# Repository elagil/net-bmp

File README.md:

# net bmp

An Ethernet-connected SWD/JTAG debug adapter, based on the [blackmagic probe](https://black-magic.org).

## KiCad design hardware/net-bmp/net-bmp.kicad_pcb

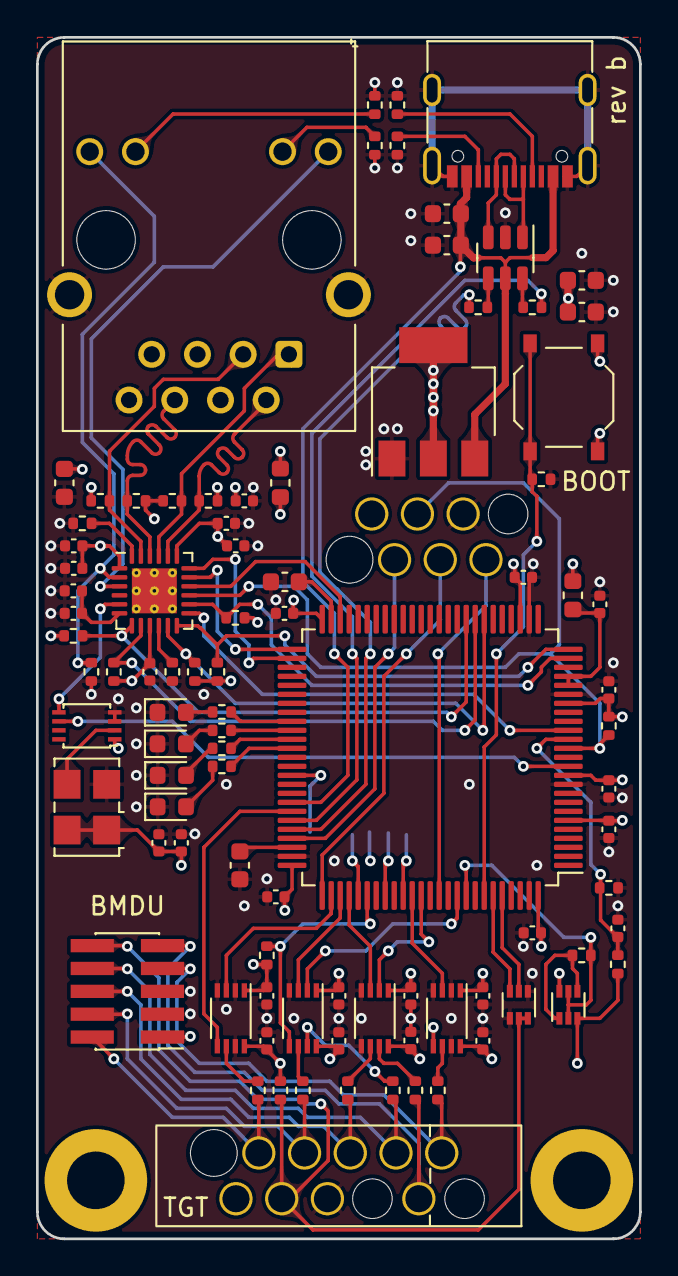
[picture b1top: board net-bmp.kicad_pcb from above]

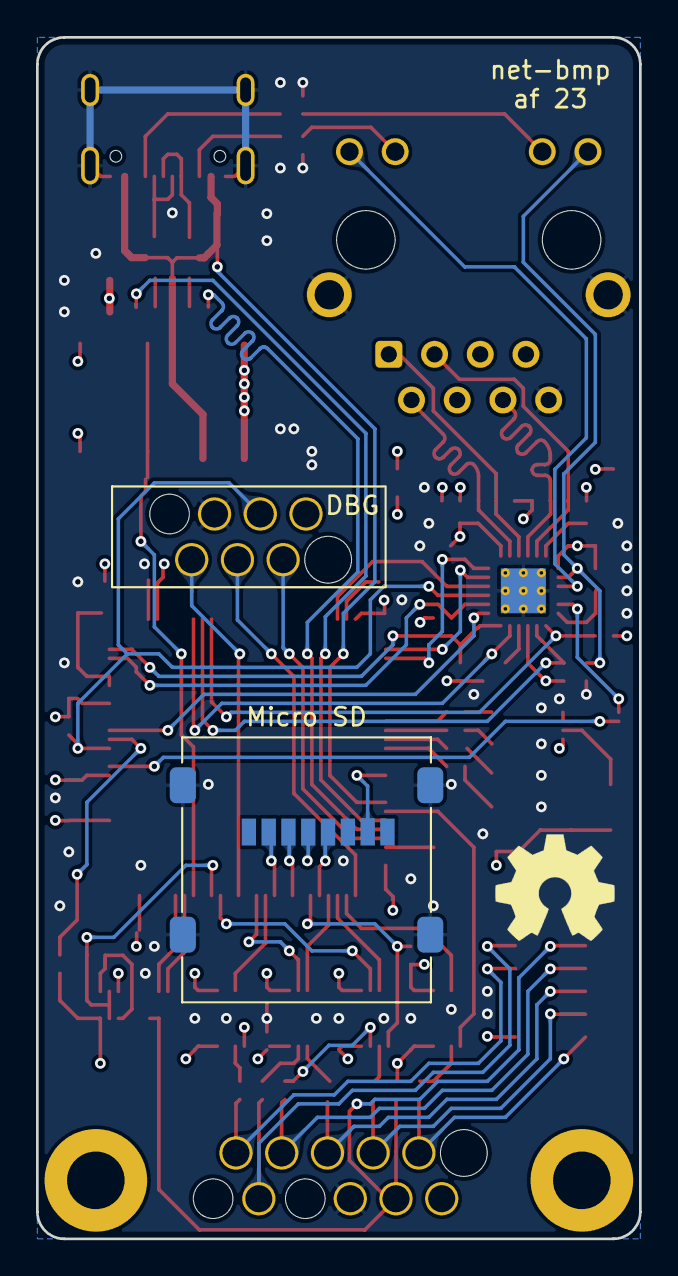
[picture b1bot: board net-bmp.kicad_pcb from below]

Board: 4 copper layers, 33.5 x 66.8 mm, 97 parts (3 on the bottom side), 82 nets.

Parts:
C1, C2, C3, C4, C5, C6, C7, C8, C11, C12, C13, C14, C15, C16, C17, C18, C21, C22, C23, C24, C25, C33, C35: 100n; C_0402_1005Metric
C9, C10: 2.2u; C_0603_1608Metric
C19: 1n; C_0402_1005Metric
C20: 1u; C_0402_1005Metric
C26, C28, C29, C30, C31: 10u; C_0603_1608Metric
C27: 22n; C_0402_1005Metric
C34: 10n; C_0402_1005Metric
D1: Blue; LED_0603_1608Metric
D2: Green; LED_0603_1608Metric
D3: Yellow; LED_0603_1608Metric
D4: Red; LED_0603_1608Metric
FB1, FB2: FerriteBead; L_0603_1608Metric
H1, H2: MountingHole; MountingHole_3.2mm_M3_ISO7380_Pad
J1: DBG; WR-WST REDFIT IDC 6 DBG
J2: Micro SD; microSD_HC_Molex_47219-2001
J4: USB_C_Receptacle_USB2.0; USB_C_Receptacle_G-Switch_GT-USB-7010ASV
J5: TGT; WR-WST REDFIT IDC 6 10 DBG
J6: BMDU; PinHeader_2x05_P1.27mm_Vertical_SMD
J7: HR911105A; RJ45_Hanrun_HR911105A
Q1, Q2: DMG1024UV-7; SOT-563
R1, R2, R7, R14, R15, R16, R17, R18, R19, R21, R35, R37: 10k; R_0402_1005Metric
R3, R4, R5, R6, R27, R28: 330; R_0402_1005Metric
R8, R9, R10, R11, R12, R13, R29, R30: 33; R_0402_1005Metric
R20: 1.5k; R_0402_1005Metric
R22: 12k; R_0402_1005Metric
R23, R24, R25, R26: 49.9; R_0402_1005Metric
R33, R34, R36: 5.1k; R_0402_1005Metric
SW1: SW_SPST; SW_Push_1P1T_XKB_TS-1187A
U1: STM32F407VETx; LQFP-100_14x14mm_P0.5mm
U2, U3, U4, U5: 74LVC2T45DC; VSSOP-8_2.3x2mm_P0.5mm
U6: LAN8742A; VQFN-24-1EP_4x4mm_P0.5mm_EP2.5x2.5mm_ThermalVias
U7: USBLC6-2SC6; SOT-23-6
U8: AMS1117-3.3; SOT-223-3_TabPin2
U9: 74AVC9112; VSSOP-8_2.4x2.1mm_P0.5mm
X2: SG-5032CCN; Oscillator_SMD_SeikoEpson_SG8002LB-4Pin_5.0x3.2mm
oshw1: Logo_Open_Hardware_Large; OSHW-Symbol_6.7x6mm_SilkScreen

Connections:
+3.3V: C1.1, C2.1, C3.1, C4.1, C5.1, C6.1, C7.1, C11.1, C12.1, C13.1, C14.1, C21.1, C30.1, C31.1, C33.1, C34.1, FB1.2, FB2.1, J1.1 (VREF), J2.4 (VDD), Q2.6 (D), R1.2, R7.2, R16.2, R17.2, R18.2, R19.2, R20.2, SW1.2 (B), U1.6 (VBAT), U1.11 (VDD), U1.19 (VDD), U1.28 (VDD), U1.50 (VDD), U1.75 (VDD), U1.100 (VDD), U2.1 (VCCA), U2.5 (DIR), U3.1 (VCCA), U4.1 (VCCA), U5.1 (VCCA), U6.9 (VDDIO), U8.2 (VO), U9.1 (VCC), X2.1 (OE), X2.4 (Vcc)
+3.3VA: C22.1, C23.1, C24.1, C25.1, C26.1, C27.2, FB1.1, J7.4, J7.5, R23.2, R24.2, R25.2, R26.2, U6.1 (VDD2A), U6.19 (VDD1A)
+3.3VP: C8.1, FB2.2, U1.21 (VREF+), U1.22 (VDDA)
/BOOT: R2.2, SW1.1 (A), U1.94 (BOOT0)
/ETH_CLK: U6.5 (XTAL1/CLKIN), U9.5 (Y1)
/ETH_CRS_DV: R18.1, U1.32 (PA7), U6.11 (CRS_DV/MODE2)
/ETH_MDC: U1.16 (PC1), U6.13 (MDC)
/ETH_MDIO: R20.1, U1.25 (PA2), U6.12 (MDIO)
/ETH_REFCLK: R19.1, U1.24 (PA1), U6.14 (~INT/REFCLKO)
/ETH_RXD0: R16.1, U1.33 (PC4), U6.8 (RXD0/MODE0)
/ETH_RXD1: R17.1, U1.34 (PC5), U6.7 (RXD1/MODE1)
/ETH_TXD0: U1.51 (PB12), U6.17 (TXD0)
/ETH_TXD1: U1.52 (PB13), U6.18 (TXD1)
/ETH_TXEN: U1.48 (PB11), U6.16 (TXEN)
/LED1: R3.2, U1.59 (PD12)
/LED2: R4.2, U1.60 (PD13)
/LED3: R5.2, U1.61 (PD14)
/LED4: R6.2, U1.62 (PD15)
/MCU_CLK: U1.12 (PH0), U9.6 (Y2)
/NRST: J1.3 (nRST), R1.1, U1.14 (NRST), U6.15 (~RST)
/PWR_BR: Q2.2 (G), Q2.5 (G), R14.2, U1.92 (PB6)
/SDIO_CD: J2.2 (DAT3/CD), U1.85 (PD4)
/SDIO_CMD: J2.3 (CMD), U1.83 (PD2)
/SDIO_D0: J2.7 (DAT0), U1.65 (PC8)
/SDIO_SCK: J2.5 (CLK), U1.80 (PC12)
/SWCLK: J1.4 (SWCLK), U1.76 (PA14)
/SWDIO: J1.2 (SWDIO), U1.72 (PA13)
/SWO: J1.6 (SWO), U1.89 (PB3)
/USB_D+: R30.1, U1.71 (PA12)
/USB_D-: R29.1, U1.70 (PA11)
/VREF_SNS: C35.1, R36.1, R37.2, U1.15 (PC0)
/debug/xRST: J5.3 (nRST), J6.10 (~RESET), Q1.5 (G), Q1.6 (D), R15.1
/debug/xRXD: J5.9 (RX), J6.9 (RX), R11.1
/debug/xTCK: J5.4 (SWCLK), J6.4 (SWDCLK/TCK), R10.1
/debug/xTDI: J5.8 (TDI), J6.8 (NC/TDI), R9.1
/debug/xTDO: J5.6 (SWO), J6.6 (SWO/TDO), R12.1
/debug/xTMS: J5.2 (SWDIO), J6.2 (SWDIO/TMS), R13.1
/debug/xTXD: J5.10 (TX), J6.7 (TX), R8.1
/ethernet/LED1: J7.9, U6.3 (LED1/REGOFF)
/ethernet/LED2: J7.12, R35.2, U6.2 (LED2/~INTSEL)
/ethernet/RXN: J7.6, R26.1, U6.22 (RXN)
/ethernet/RXP: J7.3, R25.1, U6.23 (RXP)
/ethernet/TXN: J7.2, R24.1, U6.20 (TXN)
/ethernet/TXP: J7.1, R23.1, U6.21 (TXP)
/ethernet/VDDCR: C19.1, C20.1, U6.6 (VDDCR)
/iRST: Q1.2 (G), U1.96 (PB9)
/iRST_SNS: Q1.3 (D), U1.95 (PB8)
/iRXD: U1.87 (PD6), U4.2 (1A)
/iTCK: U1.78 (PC10), U3.3 (2A)
/iTCKDI_DIR: R7.1, U1.81 (PD0), U3.5 (DIR)
/iTDI: U1.91 (PB5), U3.2 (1A)
/iTDO: U1.79 (PC11), U4.3 (2A)
/iTMS: U1.77 (PA15), U5.3 (2A)
/iTMS_DIR: U1.69 (PA10), U5.5 (DIR)
/iTXD: U1.86 (PD5), U2.3 (2A)
/usb/CC1: J4.A5 (CC1), R33.2
/usb/CC2: J4.B5 (CC2), R34.2
GND: C1.2, C2.2, C3.2, C4.2, C5.2, C6.2, C7.2, C8.2, C9.1, C10.1, C11.2, C12.2, C13.2, C14.2, C15.2, C16.2, C17.2, C18.2, C19.2, C20.2, C21.2, C22.2, C23.2, C24.2, C25.2, C26.2, C27.1, C28.2, C29.2, C30.2, C31.2, C33.2, C34.2, C35.2, D1.1 (K), D2.1 (K), D3.1 (K), D4.1 (K), J1.5 (GND), J2.6 (VSS), J2.9 (SHIELD), J4.A1 (GND), J4.A12 (GND), J4.B1 (GND), J4.B12 (GND), J4.S1 (SHIELD), J5.5 (GND), J6.3 (GND), J6.5 (GND), J7.8, J7.SH, Q1.1 (S), Q1.4 (S), R2.1, R21.1, R22.1, R27.1, R28.1, R33.1, R34.1, R35.1, R37.1, U1.10 (VSS), U1.20 (VSSA), U1.27 (VSS), U1.74 (VSS), U1.99 (VSS), U2.2 (1A), U2.4 (GND), U2.7 (1B), U3.4 (GND), U4.4 (GND), U4.5 (DIR), U5.2 (1A), U5.4 (GND), U5.7 (1B), U6.25 (VSS), U7.2 (GND), U8.1 (GND), U9.3 (NOE), U9.4 (GND), X2.2 (GND)
unnamed: D1.2 (A), R3.1
unnamed: D2.2 (A), R4.1
unnamed: D3.2 (A), R5.1
unnamed: D4.2 (A), R6.1
unnamed: J4.A6 (D+), J4.B6 (D+), U7.3 (I/O2)
unnamed: J4.A7 (D-), J4.B7 (D-), U7.1 (I/O1)
unnamed: J7.10, R27.2
unnamed: J7.11, R28.2
unnamed: Q2.1 (S), Q2.4 (S), R14.1
unnamed: R29.2, U7.6 (I/O1)
unnamed: R30.2, U7.4 (I/O2)
unnamed: C9.2, U1.49 (VCAP_1)
unnamed: C10.2, U1.73 (VCAP_2)
unnamed: R8.2, U2.6 (2B)
unnamed: R9.2, U3.7 (1B)
unnamed: R10.2, U3.6 (2B)
unnamed: R11.2, U4.7 (1B)
unnamed: R12.2, U4.6 (2B)
unnamed: R13.2, U5.6 (2B)
unnamed: R22.2, U6.24 (RBIAS)
unnamed: R21.2, U6.10 (RXER/PHYAD0)
unnamed: U9.2 (A), X2.3 (OUT)
VBUS: C28.1, C29.1, J4.A4 (VBUS), J4.A9 (VBUS), J4.B4 (VBUS), J4.B9 (VBUS), U1.68 (PA9), U8.3 (VI)
VREF: C15.1, C16.1, C17.1, C18.1, J5.1 (VREF), J6.1 (VTref), Q2.3 (D), R15.2, R36.2, U2.8 (VCCB), U3.8 (VCCB), U4.8 (VCCB), U5.8 (VCCB)

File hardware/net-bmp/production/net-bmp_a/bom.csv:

Designator,Footprint,Quantity,Value,LCSC Part #
"C1, C11, C12, C13, C14, C15, C16, C17, C18, C2, C21, C22, C23, C24, C25, C3, C33, C35, C4, C5, C6, C7, C8",0402,23,100n,C1525
"C10, C9",0603,2,2.2u,C23630
C19,0402,1,1n,C1523
C20,0402,1,1u,C52923
"C26, C28, C29, C30, C31",0603,5,10u,C19702
C27,0402,1,22n,C1532
C34,0402,1,10n,C15195
D1,0603,1,Blue,C72041
D2,0603,1,Green,C72043
D3,0603,1,Yellow,C72038
D4,0603,1,Red,C2286
"FB1, FB2",0603,2,FerriteBead,C1002
J1,WR-WST REDFIT IDC 6 DBG,1,DBG,
J2,microSD_HC_Molex_47219-2001,1,Micro SD,
J4,USB_C_Receptacle_G-Switch_GT-USB-7010ASV,1,USB_C_Receptacle_USB2.0,C963413
J5,WR-WST REDFIT IDC 6 10 DBG,1,TGT,
J6,PinHeader_2x05_P1.27mm_Vertical_SMD,1,BMDU,C2972785
J7,RJ45_Hanrun_HR911105A,1,HR911105A,C12074
"Q1, Q2",SOT-563,2,DMG1024UV-7,C2759893
"R1, R14, R15, R16, R17, R18, R19, R2, R21, R32, R37, R7",0402,12,10k,C25744
"R10, R11, R12, R13, R29, R30, R8, R9",0402,8,33,C25105
R20,0402,1,1.5k,C25867
R22,0402,1,12k,C25752
"R23, R24, R25, R26",0402,4,49.9,C25120
"R27, R28, R3, R4, R5, R6",0402,6,330,C25104
"R31, R33, R34, R36",0402,4,5.1k,C25905
SW1,SW_Push_1P1T_XKB_TS-1187A,1,SW_SPST,C318884
U1,LQFP-100_14x14mm_P0.5mm,1,STM32F407VETx,C28730
"U2, U3, U4, U5",VSSOP-8_2.3x2mm_P0.5mm,4,74LVC2T45DC,C730237
U6,VQFN-24-1EP_4x4mm_P0.5mm_EP2.5x2.5mm_ThermalVias,1,LAN8742A,C621425
U7,SOT-23-6,1,USBLC6-2SC6,C7519
U8,SOT-223-3_TabPin2,1,AMS1117-3.3,C6186
U9,VSSOP-8_2.4x2.1mm_P0.5mm,1,74AVC9112,C546283
X2,Oscillator_SMD_SeikoEpson_SG8002LB-4Pin_5.0x3.2mm,1,SG-5032CCN,C254223

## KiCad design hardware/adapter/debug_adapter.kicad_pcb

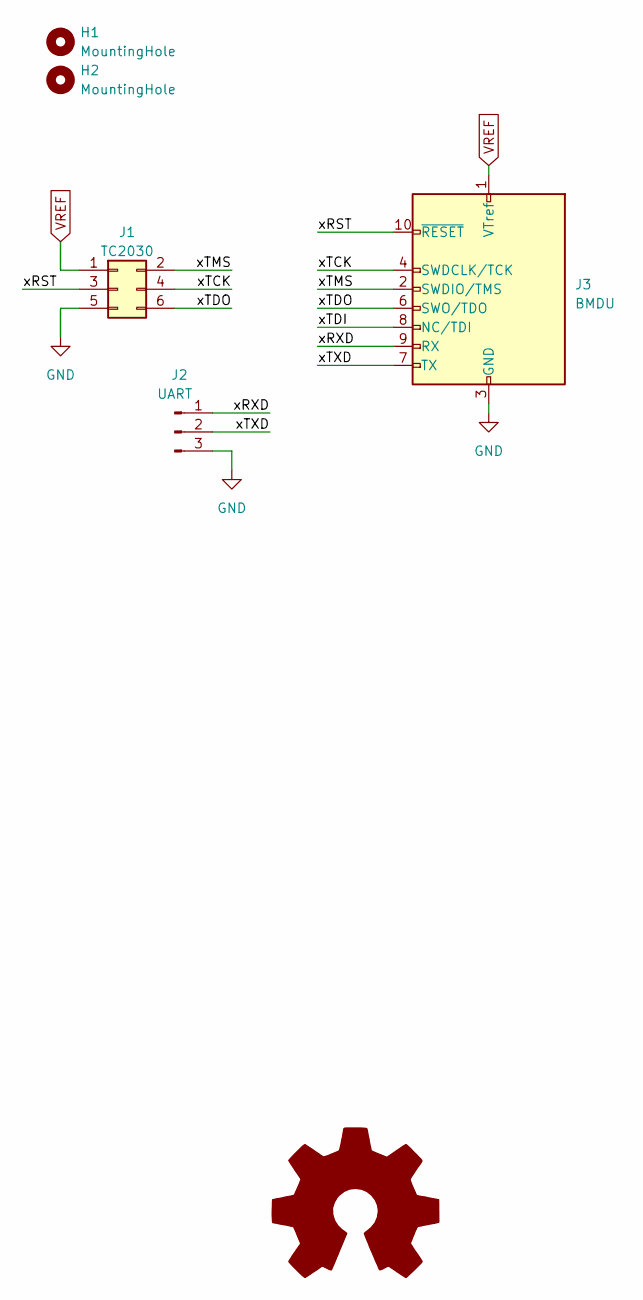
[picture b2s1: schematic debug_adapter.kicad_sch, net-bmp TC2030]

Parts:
H1, H2: MountingHole; MountingHole_3.2mm_M3_ISO7380_Pad
J1: TC2030; IDC-Header_2x03_P2.54mm_Vertical
J2: UART; PinHeader_1x03_P2.54mm_Vertical
J3: BMDU; PinSocket_2x05_P1.27mm_Vertical_SMD
oshw1: Logo_Open_Hardware_Large; OSHW-Symbol_6.7x6mm_SilkScreen

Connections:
/xRST: J1.3, J3.10 (~RESET)
/xRXD: J2.1, J3.9 (RX)
/xTCK: J1.4, J3.4 (SWDCLK/TCK)
/xTDI: J3.8 (NC/TDI)
/xTDO: J1.6, J3.6 (SWO/TDO)
/xTMS: J1.2, J3.2 (SWDIO/TMS)
/xTXD: J2.2, J3.7 (TX)
GND: J1.5, J2.3, J3.3 (GND), J3.5 (GND)
VREF: J1.1, J3.1 (VTref)

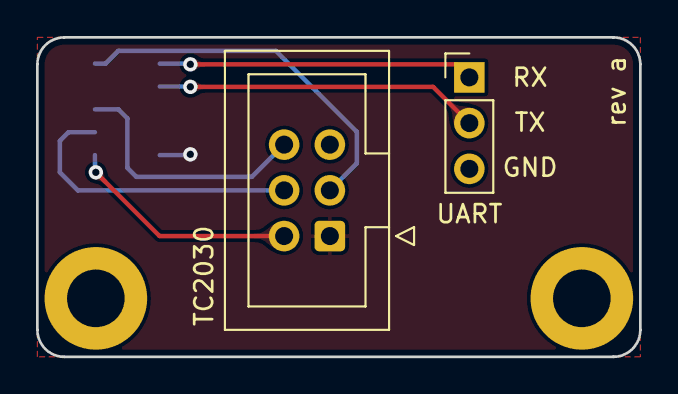
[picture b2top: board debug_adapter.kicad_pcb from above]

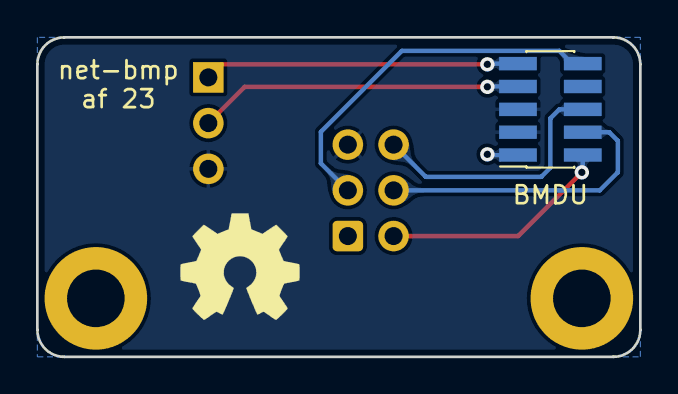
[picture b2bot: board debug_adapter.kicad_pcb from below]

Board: 2 copper layers, 33.5 x 17.8 mm, 6 parts (2 on the bottom side), 8 nets.

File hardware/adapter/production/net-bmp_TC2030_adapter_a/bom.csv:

Designator,Footprint,Quantity,Value,LCSC Part #
"H1, H2",MountingHole_3.2mm_M3_ISO7380_Pad,2,MountingHole,
J1,IDC-Header_2x03_P2.54mm_Vertical,1,TC2030,
J2,PinHeader_1x03_P2.54mm_Vertical,1,UART,
J3,PinSocket_2x05_P1.27mm_Vertical_SMD,1,BMDU,
oshw1,OSHW-Symbol_6.7x6mm_SilkScreen,1,Logo_Open_Hardware_Large,

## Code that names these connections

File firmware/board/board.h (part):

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 * GPIOA setup:
 *
 * PA0  - PIN0                      (input pullup).
 * PA1  - ETH_RMII_REF_CLK          (alternate 11).
 * PA2  - ETH_RMII_MDIO             (alternate 11).
 * PA3  - VBUS                      (analog input).
 * PA4  - PIN4                      (input pullup).
 * PA5  - PIN5                      (input pullup).
 * PA6  - PIN6                      (input pullup).
 * PA7  - ETH_RMII_CRS_DV           (alternate 11).
 * PA8  - PIN8                      (input pullup).
 * PA9  - PIN9                      (input pullup).
 * PA10 - ITMS_DIR                  (output).
 * PA11 - OTG_FS_DM                 (alternate 10).
 * PA12 - OTG_FS_DP                 (alternate 10).
 * PA13 - SWDIO                     (alternate 0).
 * PA14 - SWCLK                     (alternate 0).
 * PA15 - ITMS                      (output).
 */
#define VAL_GPIOA_MODER                                                                                                \
    (PIN_MODE_INPUT(GPIOA_PIN0) | PIN_MODE_ALTERNATE(GPIOA_ETH_RMII_REF_CLK) |                                         \
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 * PB0  - PIN0                      (input pullup).
 * PB1  - PIN1                      (input pullup).
 * PB2  - PIN2                      (input pullup).
 * PB3  - SWO                       (alternate 0).
 * PB4  - PIN4                      (input pullup).
 * PB5  - ITDI                      (output).
 * PB6  - PWR_BR                    (output).
 * PB7  - PIN7                      (input pullup).
 * PB8  - IRST_SENSE                (input floating).
 * PB9  - IRST                      (output).
 * PB10 - PIN10                     (input pullup).
 * PB11 - ETH_TXEN                  (alternate 11).
 * PB12 - ETH_TXD0                  (alternate 11).
 * PB13 - ETH_TXD1                  (alternate 11).
 * PB14 - PIN14                     (input pullup).
 * PB15 - PIN15                     (input pullup).
 */
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/*
 * GPIOC setup:
 *
 * PC0  - VREF_SENSE                (input floating).
 * PC1  - ETH_RMII_MDC              (alternate 11).
 * PC2  - PIN2                      (input pullup).
 * PC3  - PIN3                      (input pullup).
 * PC4  - ETH_RMII_RXD0             (alternate 11).
 * PC5  - ETH_RMII_RXD1             (alternate 11).
 * PC6  - PIN6                      (input pullup).
 * PC7  - PIN7                      (input pullup).
 * PC8  - SDIO_D0                   (alternate 12).
 * PC9  - PIN9                      (input pullup).
 * PC10 - PIN10                     (input pullup).
 * PC11 - PIN11                     (input pullup).
 * PC12 - SDIO_SCK                  (alternate 12).
 * PC13 - PIN13                     (input pullup).
 * PC14 - OSC32_IN                  (input floating).
 * PC15 - OSC32_OUT                 (input floating).
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/*
 * GPIOD setup:
 *
 * PD0  - ITCKDI_DIR                (output).
 * PD1  - PIN1                      (input pullup).
 * PD2  - SDIO_CMD                  (alternate 12).
 * PD3  - PIN3                      (input pullup).
 * PD4  - SDIO_CD                   (input pullup).
 * PD5  - ITXD                      (alternate 7).
 * PD6  - IRXD                      (alternate 7).
 * PD7  - PIN7                      (input pullup).
 * PD8  - PIN8                      (input pullup).
 * PD9  - PIN9                      (input pullup).
 * PD10 - PIN10                     (input pullup).
 * PD11 - PIN11                     (input pullup).
 * PD12 - LED_BLUE                      (output).
 * PD13 - LED_GREEN                      (output).
 * PD14 - LED_AMBER                      (output).
 * PD15 - LED_RED                      (output).
 */
#define VAL_GPIOD_MODER                                                                                                \
    (PIN_MODE_OUTPUT(GPIOD_ITCKDI_DIR) | PIN_MODE_INPUT(GPIOD_PIN1) | PIN_MODE_ALTERNATE(GPIOD_SDIO_CMD) |             \
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/*
 * GPIOH setup:
 *
 * PH0  - OSC_IN                    (input floating).
 * PH1  - OSC_OUT                   (input floating).
 * PH2  - PIN2                      (input pullup).
 * PH3  - PIN3                      (input pullup).
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
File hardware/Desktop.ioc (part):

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Mcu.Name=STM32F407V(E-G)Tx
Mcu.Package=LQFP100
Mcu.UserName=STM32F407VETx
PA1.Mode=RMII
PA1.Signal=ETH_REF_CLK
PA11.Mode=Device_Only
PA11.Signal=USB_OTG_FS_DM
PA12.Mode=Device_Only
PA12.Signal=USB_OTG_FS_DP
PA13.Mode=Serial_Wire
PA13.Signal=SYS_JTMS-SWDIO
PA14.Mode=Serial_Wire
PA14.Signal=SYS_JTCK-SWCLK
PA2.Mode=RMII
PA2.Signal=ETH_MDIO
PA7.Mode=RMII
PA7.Signal=ETH_CRS_DV
PB11.Mode=RMII
PB11.Signal=ETH_TX_EN
PB12.Mode=RMII
PB12.Signal=ETH_TXD0
PB13.Mode=RMII
PB13.Signal=ETH_TXD1
PC1.Mode=RMII
PC1.Signal=ETH_MDC
PC4.Mode=RMII
PC4.Signal=ETH_RXD0
PC5.Mode=RMII
PC5.Signal=ETH_RXD1
PH0-OSC_IN.Mode=HSE-External-Clock-Source
PH0-OSC_IN.Signal=RCC_OSC_IN
PH1-OSC_OUT.Mode=HSE-External-Clock-Source
PH1-OSC_OUT.Signal=RCC_OSC_OUT
RCC.HSE_VALUE=25000000
RCC.SYSCLKFreq_VALUE=168000000
RCC.SYSCLKSource=RCC_SYSCLKSOURCE_PLLCLK
board=custom

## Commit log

2023-10-20 chore: initialize repository
2023-11-01 feat: revision a manufacture
2023-11-01 chore: do not exclude bom files
2023-11-01 docs: update readme
2023-11-01 chore: first build and tooling
2023-11-01 docs: add image
2023-11-01 style: linting and formatting
2023-11-01 chore: add lwip to build
2023-11-01 chore: move to tagged submodules
2023-11-06 [pre-commit.ci] pre-commit autoupdate
    updates:
    - [github.com/pre-commit/mirrors-clang-format: v16.0.4 → v17.0.4](https://github.com/pre-commit/mirrors-clang-format/compare/v16.0.4...v17.0.4)
    - [github.com/pre-commit/pre-commit-hooks: v4.4.0 → v4.5.0](https://github.com/pre-commit/pre-commit-hooks/compare/v4.4.0...v4.5.0)
    - [github.com/crate-ci/typos: v1.14.11 → v1.16.23](https://github.com/crate-ci/typos/compare/v1.14.11...v1.16.23)
2023-11-06 [pre-commit.ci] auto fixes from pre-commit.com hooks
    for more information, see https://pre-commit.ci
2023-11-15 chore: build with stubs
2023-11-29 feat: wip, initial gdb server
2023-12-03 feat: improve query module
2023-12-05 refactor: simplify module naming
2023-12-05 chore: unify include guards
2023-12-06 fix: build with target modules
2023-12-06 refactor: simplify GDB reply messages, improve naming
2023-12-18 [pre-commit.ci] pre-commit autoupdate
    updates:
    - [github.com/pre-commit/mirrors-clang-format: v17.0.4 → v17.0.6](https://github.com/pre-commit/mirrors-clang-format/compare/v17.0.4...v17.0.6)
    - [github.com/crate-ci/typos: v1.16.23 → v1.16.25](https://github.com/crate-ci/typos/compare/v1.16.23...v1.16.25)
2024-01-01 [pre-commit.ci] pre-commit autoupdate
    updates:
    - [github.com/crate-ci/typos: v1.16.25 → v1.16.26](https://github.com/crate-ci/typos/compare/v1.16.25...v1.16.26)
2024-01-08 [pre-commit.ci] pre-commit autoupdate
    updates:
    - [github.com/crate-ci/typos: v1.16.25 → v1.17.0](https://github.com/crate-ci/typos/compare/v1.16.25...v1.17.0)
2024-02-05 [pre-commit.ci] pre-commit autoupdate
    updates:
    - [github.com/crate-ci/typos: v1.17.0 → v1.18.1](https://github.com/crate-ci/typos/compare/v1.17.0...v1.18.1)
2024-02-20 [pre-commit.ci] pre-commit autoupdate
    updates:
    - [github.com/crate-ci/typos: v1.18.1 → typos-v0.10.21](https://github.com/crate-ci/typos/compare/v1.18.1...typos-v0.10.21)
2024-03-13 [pre-commit.ci] pre-commit autoupdate
    updates:
    - [github.com/pre-commit/mirrors-clang-format: v17.0.6 → v18.1.1](https://github.com/pre-commit/mirrors-clang-format/compare/v17.0.6...v18.1.1)
    - [github.com/crate-ci/typos: typos-v0.10.21 → v1.19.0](https://github.com/crate-ci/typos/compare/typos-v0.10.21...v1.19.0)
2024-03-25 [pre-commit.ci] pre-commit autoupdate
    updates:
    - [github.com/pre-commit/mirrors-clang-format: v18.1.1 → v18.1.2](https://github.com/pre-commit/mirrors-clang-format/compare/v18.1.1...v18.1.2)
2024-04-01 [pre-commit.ci] pre-commit autoupdate
    updates:
    - [github.com/pre-commit/mirrors-clang-format: v18.1.1 → v18.1.2](https://github.com/pre-commit/mirrors-clang-format/compare/v18.1.1...v18.1.2)
    - [github.com/crate-ci/typos: v1.19.0 → v1.20.1](https://github.com/crate-ci/typos/compare/v1.19.0...v1.20.1)
2024-04-29 [pre-commit.ci] pre-commit autoupdate
    updates:
    - [github.com/pre-commit/mirrors-clang-format: v18.1.2 → v18.1.4](https://github.com/pre-commit/mirrors-clang-format/compare/v18.1.2...v18.1.4)
    - [github.com/pre-commit/pre-commit-hooks: v4.5.0 → v4.6.0](https://github.com/pre-commit/pre-commit-hooks/compare/v4.5.0...v4.6.0)
    - [github.com/crate-ci/typos: v1.20.1 → v1.20.10](https://github.com/crate-ci/typos/compare/v1.20.1...v1.20.10)
2024-05-06 [pre-commit.ci] pre-commit autoupdate
    updates:
    - [github.com/crate-ci/typos: v1.20.10 → v1.21.0](https://github.com/crate-ci/typos/compare/v1.20.10...v1.21.0)
2024-05-13 [pre-commit.ci] pre-commit autoupdate
    updates:
    - [github.com/pre-commit/mirrors-clang-format: v18.1.4 → v18.1.5](https://github.com/pre-commit/mirrors-clang-format/compare/v18.1.4...v18.1.5)
2024-06-10 [pre-commit.ci] pre-commit autoupdate
    updates:
    - [github.com/pre-commit/mirrors-clang-format: v18.1.5 → v18.1.6](https://github.com/pre-commit/mirrors-clang-format/compare/v18.1.5...v18.1.6)
    - [github.com/crate-ci/typos: v1.21.0 → v1.22.4](https://github.com/crate-ci/typos/compare/v1.21.0...v1.22.4)
2024-06-17 [pre-commit.ci] pre-commit autoupdate
    updates:
    - [github.com/crate-ci/typos: v1.22.4 → v1.22.7](https://github.com/crate-ci/typos/compare/v1.22.4...v1.22.7)
2024-07-02 [pre-commit.ci] pre-commit autoupdate
    updates:
    - [github.com/pre-commit/mirrors-clang-format: v18.1.6 → v18.1.8](https://github.com/pre-commit/mirrors-clang-format/compare/v18.1.6...v18.1.8)
    - [github.com/crate-ci/typos: v1.22.7 → v1.22.9](https://github.com/crate-ci/typos/compare/v1.22.7...v1.22.9)
2024-07-22 [pre-commit.ci] pre-commit autoupdate
    updates:
    - [github.com/pre-commit/mirrors-clang-format: v18.1.6 → v18.1.8](https://github.com/pre-commit/mirrors-clang-format/compare/v18.1.6...v18.1.8)
    - [github.com/crate-ci/typos: v1.22.7 → v1.23.3](https://github.com/crate-ci/typos/compare/v1.22.7...v1.23.3)
2024-07-29 [pre-commit.ci] pre-commit autoupdate
    updates:
    - [github.com/crate-ci/typos: v1.23.3 → v1.23.5](https://github.com/crate-ci/typos/compare/v1.23.3...v1.23.5)
2024-08-05 [pre-commit.ci] pre-commit autoupdate
    updates:
    - [github.com/crate-ci/typos: v1.23.5 → v1.23.6](https://github.com/crate-ci/typos/compare/v1.23.5...v1.23.6)
2024-08-26 [pre-commit.ci] pre-commit autoupdate
    updates:
    - [github.com/crate-ci/typos: v1.23.6 → v1.24.1](https://github.com/crate-ci/typos/compare/v1.23.6...v1.24.1)
2024-09-02 [pre-commit.ci] pre-commit autoupdate
    updates:
    - [github.com/crate-ci/typos: v1.24.1 → typos-dict-v0.11.27](https://github.com/crate-ci/typos/compare/v1.24.1...typos-dict-v0.11.27)
2024-09-09 [pre-commit.ci] pre-commit autoupdate
    updates:
    - [github.com/crate-ci/typos: typos-dict-v0.11.27 → v1.24.5](https://github.com/crate-ci/typos/compare/typos-dict-v0.11.27...v1.24.5)
2024-09-16 [pre-commit.ci] pre-commit autoupdate
    updates:
    - [github.com/crate-ci/typos: v1.24.5 → v1.24.6](https://github.com/crate-ci/typos/compare/v1.24.5...v1.24.6)
2024-09-30 [pre-commit.ci] pre-commit autoupdate
    updates:
    - [github.com/pre-commit/mirrors-clang-format: v18.1.8 → v19.1.0](https://github.com/pre-commit/mirrors-clang-format/compare/v18.1.8...v19.1.0)
2024-10-08 [pre-commit.ci] pre-commit autoupdate
    updates:
    - [github.com/pre-commit/mirrors-clang-format: v19.1.0 → v19.1.1](https://github.com/pre-commit/mirrors-clang-format/compare/v19.1.0...v19.1.1)
    - [github.com/pre-commit/pre-commit-hooks: v4.6.0 → v5.0.0](https://github.com/pre-commit/pre-commit-hooks/compare/v4.6.0...v5.0.0)
    - [github.com/cpplint/cpplint: 1.6.1 → 2.0.0](https://github.com/cpplint/cpplint/compare/1.6.1...2.0.0)
    - [github.com/crate-ci/typos: v1.24.6 → v1.26.0](https://github.com/crate-ci/typos/compare/v1.24.6...v1.26.0)
2024-10-21 [pre-commit.ci] pre-commit autoupdate
    updates:
    - [github.com/pre-commit/mirrors-clang-format: v19.1.1 → v19.1.2](https://github.com/pre-commit/mirrors-clang-format/compare/v19.1.1...v19.1.2)
2024-10-28 [pre-commit.ci] pre-commit autoupdate
    updates:
    - [github.com/crate-ci/typos: v1.26.0 → v1.26.8](https://github.com/crate-ci/typos/compare/v1.26.0...v1.26.8)
2024-11-04 [pre-commit.ci] pre-commit autoupdate
    updates:
    - [github.com/pre-commit/mirrors-clang-format: v19.1.2 → v19.1.3](https://github.com/pre-commit/mirrors-clang-format/compare/v19.1.2...v19.1.3)
    - [github.com/crate-ci/typos: v1.26.8 → v1.27.0](https://github.com/crate-ci/typos/compare/v1.26.8...v1.27.0)
2024-11-11 [pre-commit.ci] pre-commit autoupdate
    updates:
    - [github.com/crate-ci/typos: v1.27.0 → typos-dict-v0.11.35](https://github.com/crate-ci/typos/compare/v1.27.0...typos-dict-v0.11.35)
2024-11-25 [pre-commit.ci] pre-commit autoupdate
    updates:
    - [github.com/pre-commit/mirrors-clang-format: v19.1.3 → v19.1.4](https://github.com/pre-commit/mirrors-clang-format/compare/v19.1.3...v19.1.4)
    - [github.com/crate-ci/typos: typos-dict-v0.11.35 → v1.28.0](https://github.com/crate-ci/typos/compare/typos-dict-v0.11.35...v1.28.0)
2024-12-02 [pre-commit.ci] pre-commit autoupdate
    updates:
    - [github.com/crate-ci/typos: v1.28.0 → typos-dict-v0.11.37](https://github.com/crate-ci/typos/compare/v1.28.0...typos-dict-v0.11.37)
2024-12-16 [pre-commit.ci] pre-commit autoupdate
    updates:
    - [github.com/pre-commit/mirrors-clang-format: v19.1.4 → v19.1.5](https://github.com/pre-commit/mirrors-clang-format/compare/v19.1.4...v19.1.5)
    - [github.com/crate-ci/typos: typos-dict-v0.11.37 → v1.28.4](https://github.com/crate-ci/typos/compare/typos-dict-v0.11.37...v1.28.4)
2025-01-07 [pre-commit.ci] pre-commit autoupdate
    updates:
    - [github.com/pre-commit/mirrors-clang-format: v19.1.5 → v19.1.6](https://github.com/pre-commit/mirrors-clang-format/compare/v19.1.5...v19.1.6)
    - [github.com/crate-ci/typos: v1.28.4 → dictgen-v0.3.1](https://github.com/crate-ci/typos/compare/v1.28.4...dictgen-v0.3.1)
2025-01-20 [pre-commit.ci] pre-commit autoupdate
    updates:
    - [github.com/pre-commit/mirrors-clang-format: v19.1.6 → v19.1.7](https://github.com/pre-commit/mirrors-clang-format/compare/v19.1.6...v19.1.7)
2025-02-04 [pre-commit.ci] pre-commit autoupdate
    updates:
    - [github.com/crate-ci/typos: dictgen-v0.3.1 → typos-dict-v0.12.4](https://github.com/crate-ci/typos/compare/dictgen-v0.3.1...typos-dict-v0.12.4)
2025-05-05 [pre-commit.ci] pre-commit autoupdate
    updates:
    - [github.com/pre-commit/mirrors-clang-format: v19.1.7 → v20.1.3](https://github.com/pre-commit/mirrors-clang-format/compare/v19.1.7...v20.1.3)
    - [github.com/cpplint/cpplint: 2.0.0 → 2.0.2](https://github.com/cpplint/cpplint/compare/2.0.0...2.0.2)
    - [github.com/crate-ci/typos: dictgen-v0.3.1 → v1](https://github.com/crate-ci/typos/compare/dictgen-v0.3.1...v1)

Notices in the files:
firmware/board/board.h:
ChibiOS - Copyright (C) 2006..2023 Giovanni Di Sirio
Licensed under the Apache License, Version 2.0 (the "License");
